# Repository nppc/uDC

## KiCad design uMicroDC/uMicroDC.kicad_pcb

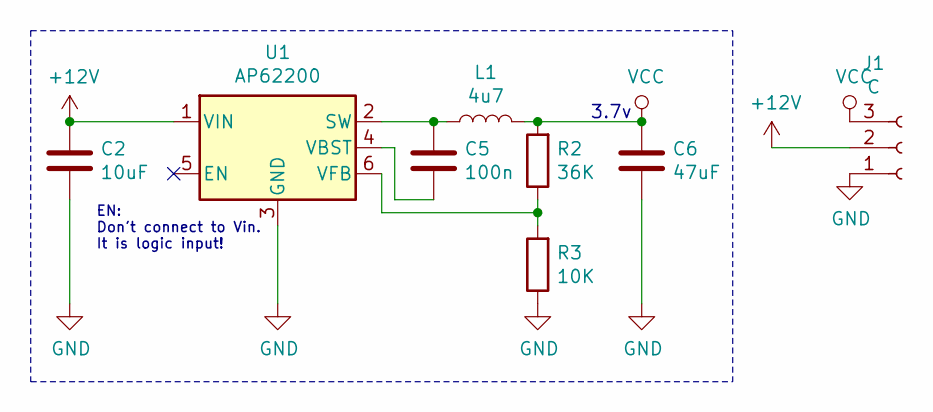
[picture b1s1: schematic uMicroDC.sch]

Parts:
C2: 10uF; C_0805
C5: 100n; C_0603
C6: 47uF; C_0805
J1: C; Pin_Header_Angled_1x03_Pitch2.54mm
L1: 4u7; XFL2006-inductor
R2: 36K; R_0603
R3: 10K; R_0603
U1: AP62200; SOT-563

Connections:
+12V: C2.1, J1.2, U1.1 (VIN)
GND: C2.2, C6.2, J1.1, R3.1, U1.3 (GND)
unnamed: C5.1, L1.1, U1.2 (SW)
unnamed: C5.2, U1.4 (VBST)
unnamed: R2.1, R3.2, U1.6 (VFB)
VCC: C6.1, J1.3, L1.2, R2.2

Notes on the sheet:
3.7v
EN: Don't connect to Vin. It is logic input!

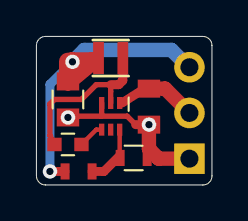
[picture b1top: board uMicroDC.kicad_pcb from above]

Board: 2 copper layers, 9.8 x 8.2 mm, 8 parts (1 on the bottom side), 6 nets.

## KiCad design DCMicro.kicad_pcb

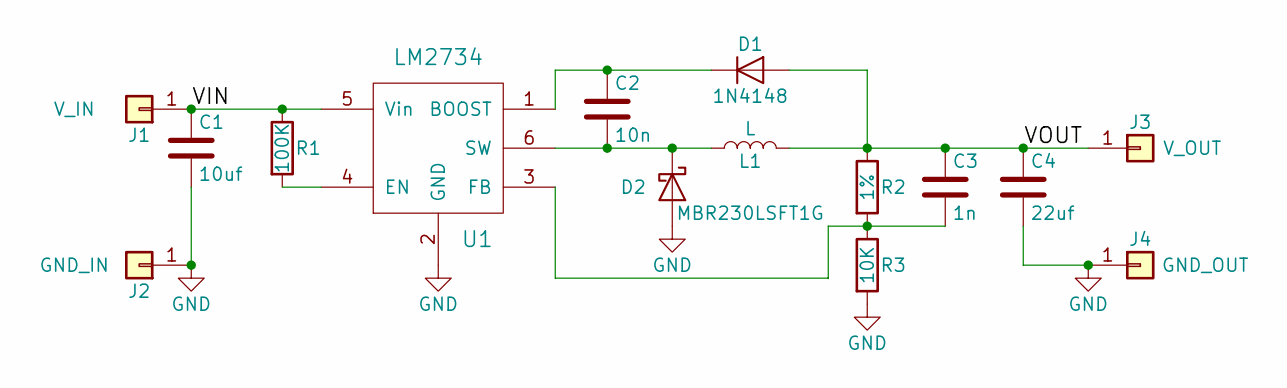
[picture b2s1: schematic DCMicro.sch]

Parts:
C1: 10uf; C_0603
C2: 10n; C_0402_NoSilk
C3: 1n; C_0402_NoSilk
C4: 22uf; C_0603
D1: 1N4148; D_SOD-523
D2: MBR230LSFT1G; D_SOD-123F
J1: V_IN; ESC_PWR_PAD
J2: GND_IN; ESC_PWR_PAD
J3: V_OUT; ESC_PWR_PAD
J4: GND_OUT; ESC_PWR_PAD
L1: L; Inductor-LPS4012
R1: 100K; R_0402_NoSilk
R2: 1%; R_0402_NoSilk
R3: 10K; R_0402_NoSilk
U1: LM2734; SOT-23-6

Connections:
/VIN: C1.1, J1.1, R1.1, U1.5 (Vin)
/VOUT: C3.1, C4.1, D1.2 (A), J3.1, L1.2, R2.1
GND: C1.2, C4.2, D2.2 (A), J2.1, J4.1, R3.2, U1.2 (GND)
unnamed: C2.1, D1.1 (K), U1.1 (BOOST)
unnamed: C2.2, D2.1 (K), L1.1, U1.6 (SW)
unnamed: C3.2, R2.2, R3.1, U1.3 (FB)
unnamed: R1.2, U1.4 (EN)

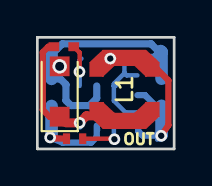
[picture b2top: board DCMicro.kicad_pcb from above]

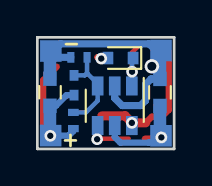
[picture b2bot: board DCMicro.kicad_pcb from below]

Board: 2 copper layers, 7.6 x 6.2 mm, 15 parts (11 on the bottom side), 7 nets.

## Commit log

2018-03-26 Initial commit from local drive
2020-11-13 Added old PCB image
2022-01-02 AP62200 PCB
